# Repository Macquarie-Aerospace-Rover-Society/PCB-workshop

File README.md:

# PCB Workshop KiCAD project

This repository holds the source files used in the KiCAD project.

## DIY

To order PCBs using KiCAD as the PCB design software from JLCPCB follow these guides ([fabrication outputs](https://jlcpcb.com/help/article/How-to-generate-the-BOM-and-Centroid-file-from-KiCAD) and [ordering](https://jlcpcb.com/help/article/how-do-i-place-a-pcba-order)). In short the process is:

1. Generate BOM.
2. Generate Gerber files.
3. Generate Drill files.
4. Generate assembly csv.
5. Modify Files.
   1. Modify BOM to have the correct format (to make ordering easier add LCSC part).
   2. Modify top assembly file to correct format.
6. Zip all gerber files and drill files together.
7. Create an account (Or use google)
8. Order from JLCPCB

To ease this process some **EXAMPLES** outputs are provided [BOM.csv](./out/BOM.csv) and [PCB_WORKSHOP_MUDS_MARS-top-pos.csv](./out/PCB_WORKSHOP_MUDS_MARS-top-pos.csv)

## Images

## Additional notes

When designing boards to be made with JLCPCB adding `JLCJLCJLCJLC` to a silkscreen layer on the board eases fabrication.
In addition adding tooling holes ([1.152mm unplated holes](https://jlcpcb.com/help/article/How-to-add-tooling-holes-for-PCB-assembly-order)) prevents JLC from placing the holes in undesirable locations.

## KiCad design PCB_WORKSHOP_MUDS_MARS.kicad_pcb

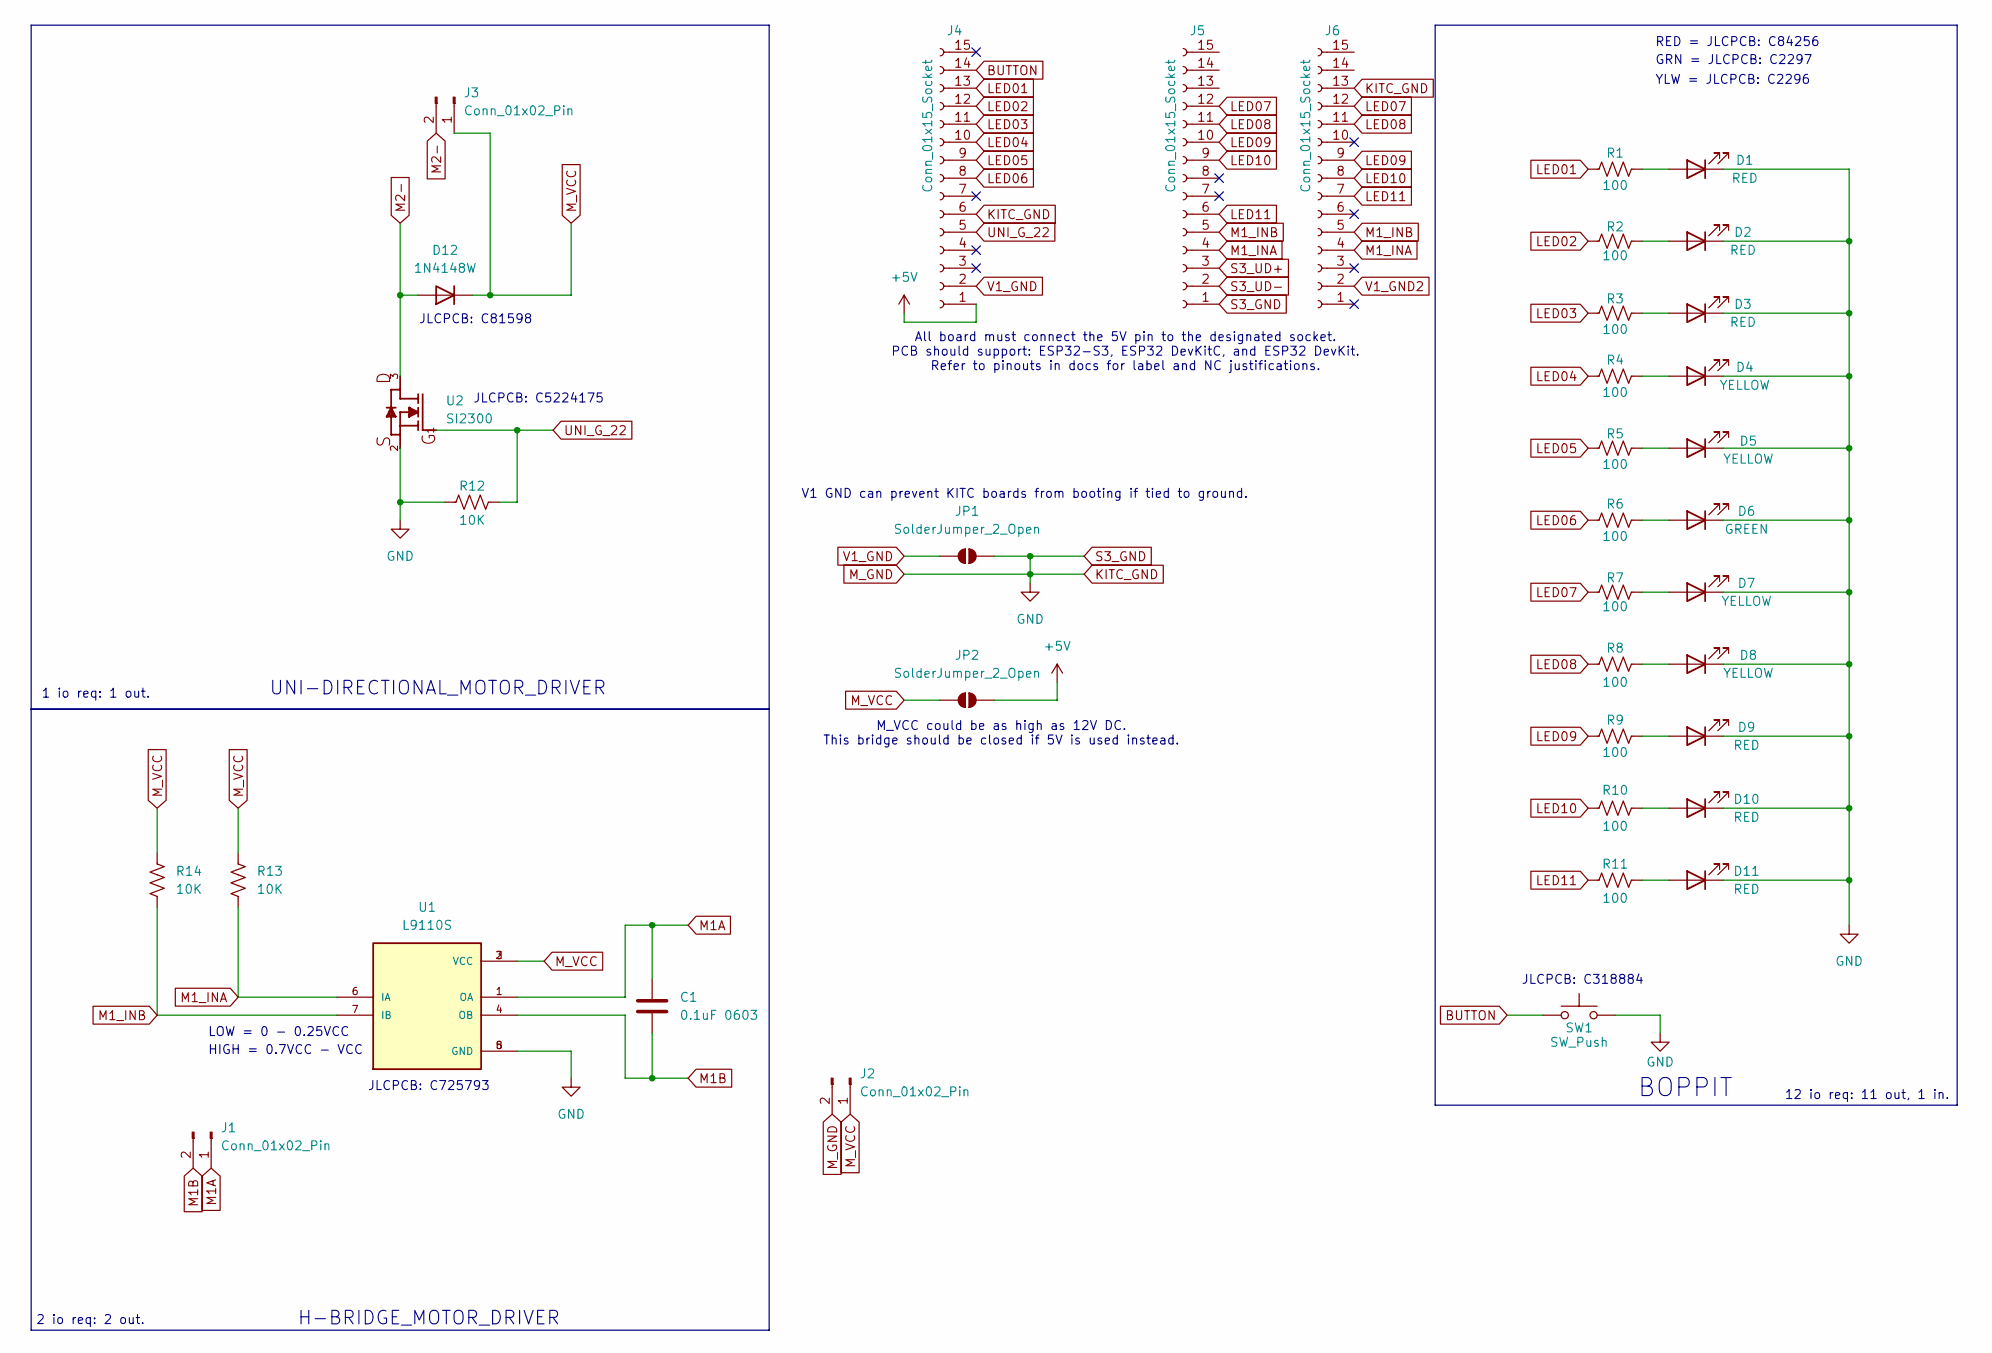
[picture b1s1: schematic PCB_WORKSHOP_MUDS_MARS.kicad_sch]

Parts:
C1: 0.1uF 0603; C_0603_1608Metric
D1, D2, D3, D9, D10, D11: RED; LED_0805_2012Metric
D4, D5, D7, D8: YELLOW; LED_0805_2012Metric
D6: GREEN; LED_0805_2012Metric
D12: 1N4148W; D_SOD-123
J1, J2, J3: Conn_01x02_Pin; TerminalBlock_Phoenix_MPT-0,5-2-2.54_1x02_P2.54mm_Horizontal
J4, J5, J6: Conn_01x15_Socket; PinSocket_1x15_P2.54mm_Vertical
JP1, JP2: SolderJumper_2_Open; SolderJumper-2_P1.3mm_Open_RoundedPad1.0x1.5mm
R1, R2, R3, R4, R5, R6, R7, R8, R9, R10, R11: 100; R_0603_1608Metric
R12, R13, R14: 10K; R_0603_1608Metric
SW1: SW_Push; SW_SPST_TL3342
U1: L9110S; SOP-8_3.76x4.96mm_P1.27mm; PARTREV NA
U2: SI2300; SOT23_1_

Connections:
+5V: J4.1, JP2.2 (B)
BUTTON: J4.14, SW1.1
KITC_GND: D1.1 (K), D2.1 (K), D3.1 (K), D4.1 (K), D5.1 (K), D6.1 (K), D7.1 (K), D8.1 (K), D9.1 (K), D10.1 (K), D11.1 (K), J2.2, J4.6, J5.1, J6.13, JP1.2 (B), R12.1, SW1.2, U1.5 (GND), U1.8 (GND), U2.2
LED01: J4.13, R1.1
LED02: J4.12, R2.1
LED03: J4.11, R3.1
LED04: J4.10, R4.1
LED05: J4.9, R5.1
LED06: J4.8, R6.1
LED07: J5.12, J6.12, R7.1
LED08: J5.11, J6.11, R8.1
LED09: J5.10, J6.9, R9.1
LED10: J5.9, J6.8, R10.1
LED11: J5.6, J6.7, R11.1
M1A: C1.1, J1.1, U1.1 (OA)
M1B: C1.2, J1.2, U1.4 (OB)
M1_INA: J5.4, J6.4, R13.1, U1.6 (IA)
M1_INB: J5.5, J6.5, R14.1, U1.7 (IB)
M2-: D12.2 (A), J3.2, U2.3
M_VCC: D12.1 (K), J2.1, J3.1, JP2.1 (A), R13.2, R14.2, U1.2 (VCC), U1.3 (VCC)
unnamed: D1.2 (A), R1.2
unnamed: D2.2 (A), R2.2
unnamed: D3.2 (A), R3.2
unnamed: D4.2 (A), R4.2
unnamed: D5.2 (A), R5.2
unnamed: D6.2 (A), R6.2
unnamed: D7.2 (A), R7.2
unnamed: D8.2 (A), R8.2
unnamed: D9.2 (A), R9.2
unnamed: D10.2 (A), R10.2
unnamed: D11.2 (A), R11.2
S3_UD+: J5.3
S3_UD-: J5.2
UNI_G_22: J4.5, R12.2, U2.1
V1_GND: J4.2, JP1.1 (A)
V1_GND2: J6.2

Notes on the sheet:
HIGH = 0.7VCC - VCC
YLW = JLCPCB: C2296
LOW = 0 - 0.25VCC
All board must connect the 5V pin to the designated socket. PCB should support: ESP32-S3, ESP32 DevKitC, and ESP32 DevKit. Refer to pinouts in docs for label and NC justifications.
V1 GND can prevent KITC boards from booting if tied to ground.
JLCPCB: C318884
UNI-DIRECTIONAL_MOTOR_DRIVER
BOPPIT
JLCPCB: C725793
JLCPCB: C81598
12 io req: 11 out, 1 in.
GRN = JLCPCB: C2297
2 io req: 2 out.
JLCPCB: C5224175
RED = JLCPCB: C84256
H-BRIDGE_MOTOR_DRIVER
1 io req: 1 out.
M_VCC could be as high as 12V DC. This bridge should be closed if 5V is used instead.

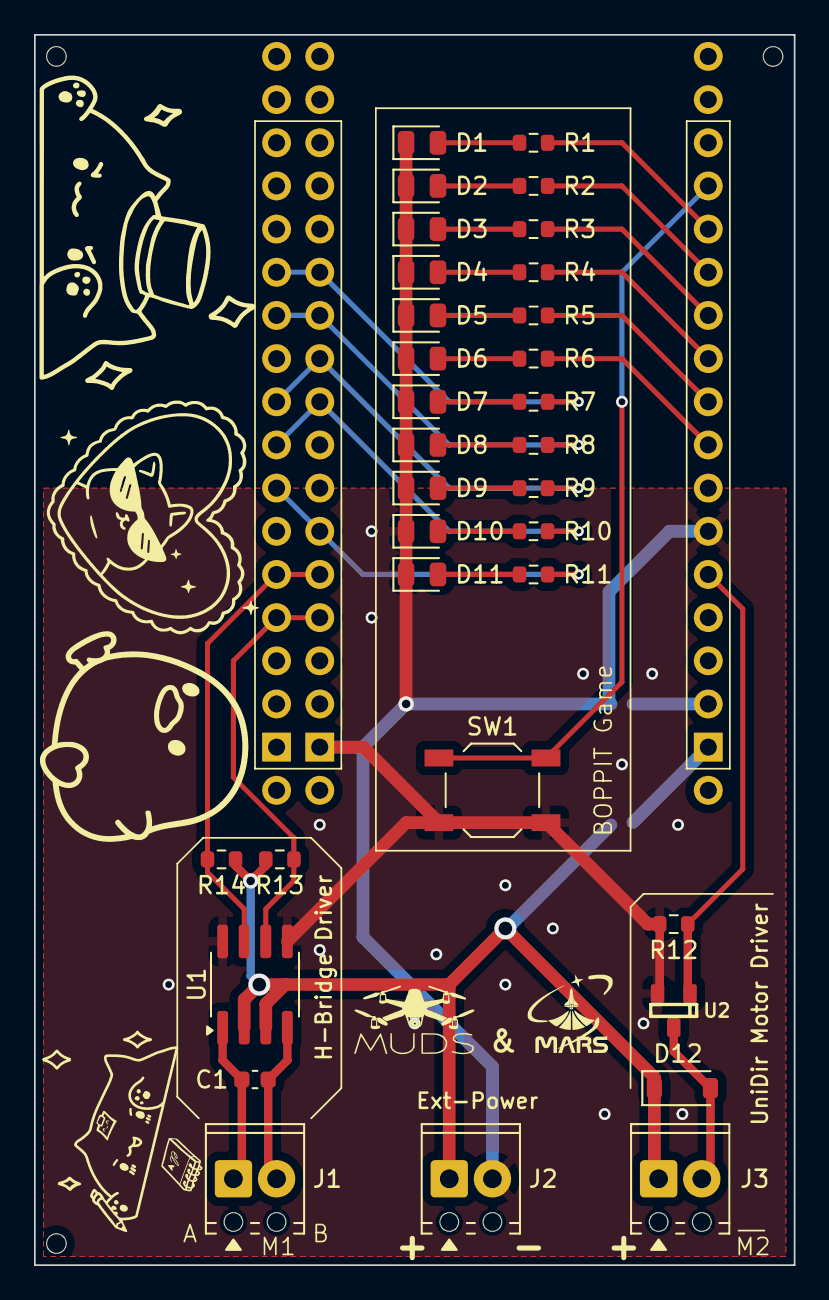
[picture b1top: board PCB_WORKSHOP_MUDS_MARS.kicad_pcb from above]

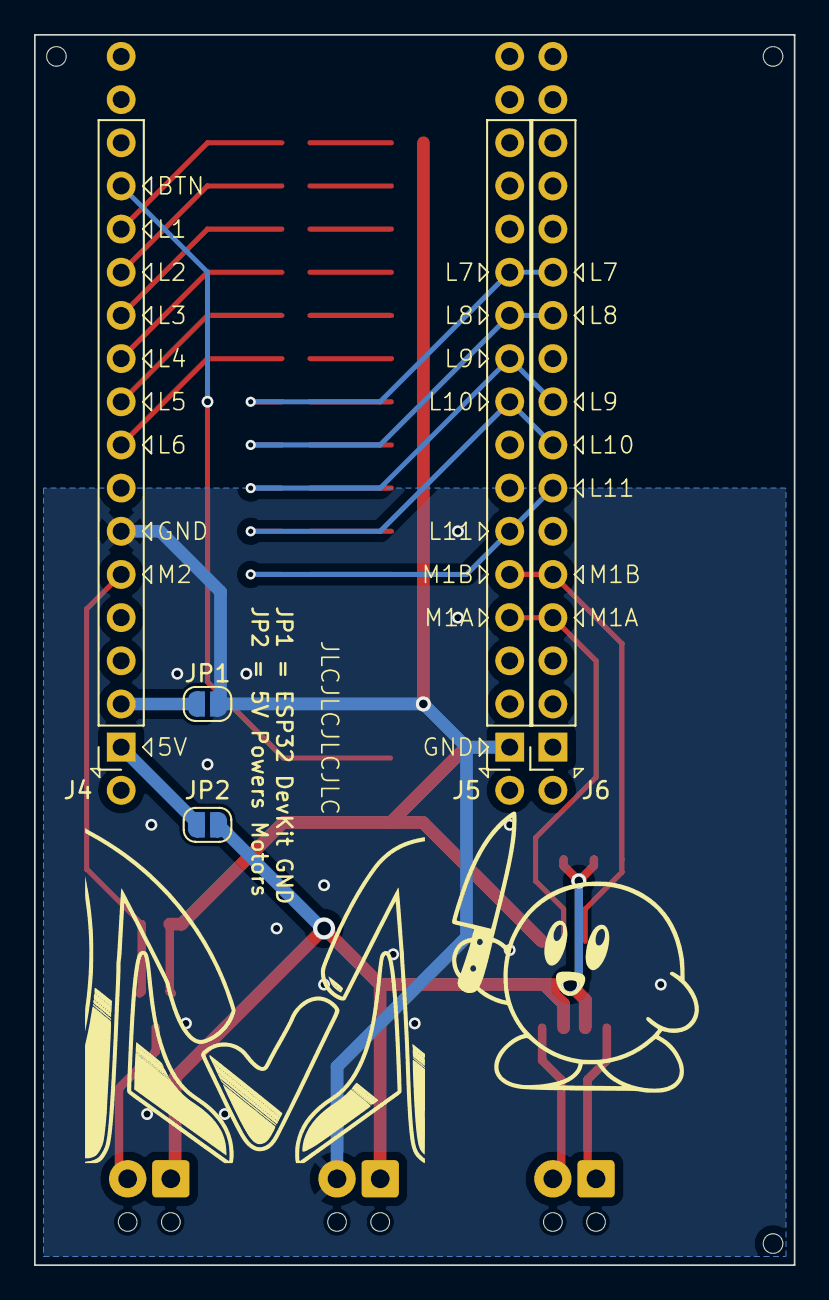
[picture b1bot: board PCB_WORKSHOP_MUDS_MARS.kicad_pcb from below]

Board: 2 copper layers, 44.7 x 72.4 mm, 38 parts (5 on the bottom side), 33 nets.

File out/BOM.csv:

Qty,Value,Designator,Footprint,LCSC Part Number
1,0.1uF,C1,603,C14663
6,RED,"D1,D2,D3,D9,D10,D11",805,C84256
4,YELLOW,"D4,D5,D7,D8",805,C2296
1,GREEN,D6,805,C2297
1,1N4148W,D12,DOD-123,C81598
1,SI2300,U2,SOT23_1_,C5224175
11,100,"R1,R2,R3,R4,R5,R6,R7,R8,R9,R10,R11",603,C22775
3,10K,"R12,R13,R14",603,C25804
1,SW_Push,SW1,Button_Switch,C318884
1,L9110S,U1,SOP-8,C725793
3,Conn_01x02_Pin,"J1,J2,J3","TerminalBlock_Phoenix:TerminalBlock_Phoenix_MPT-0,5-2-2.54_1x02_P2.54mm_Horizontal",
3,Conn_01x15_Socket,"J4,J5,J6",Connector_PinSocket_2.54mm:PinSocket_1x15_P2.54mm_Vertical,

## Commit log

2025-09-01 Initial commit: Board complete need more documentation for workshop
2025-09-01 Added license
2025-09-01 Rename LICENSE.txt to LICENSE.md
2025-09-05 Added explicit JLCPCB parts for jelly beans to ease ordering
2025-09-16 Silk screen adjustments
2025-09-16 added README, fixed examples
2025-09-16 Forgot silkscreen blocks
2025-09-16 Custom silkscreen images for order
